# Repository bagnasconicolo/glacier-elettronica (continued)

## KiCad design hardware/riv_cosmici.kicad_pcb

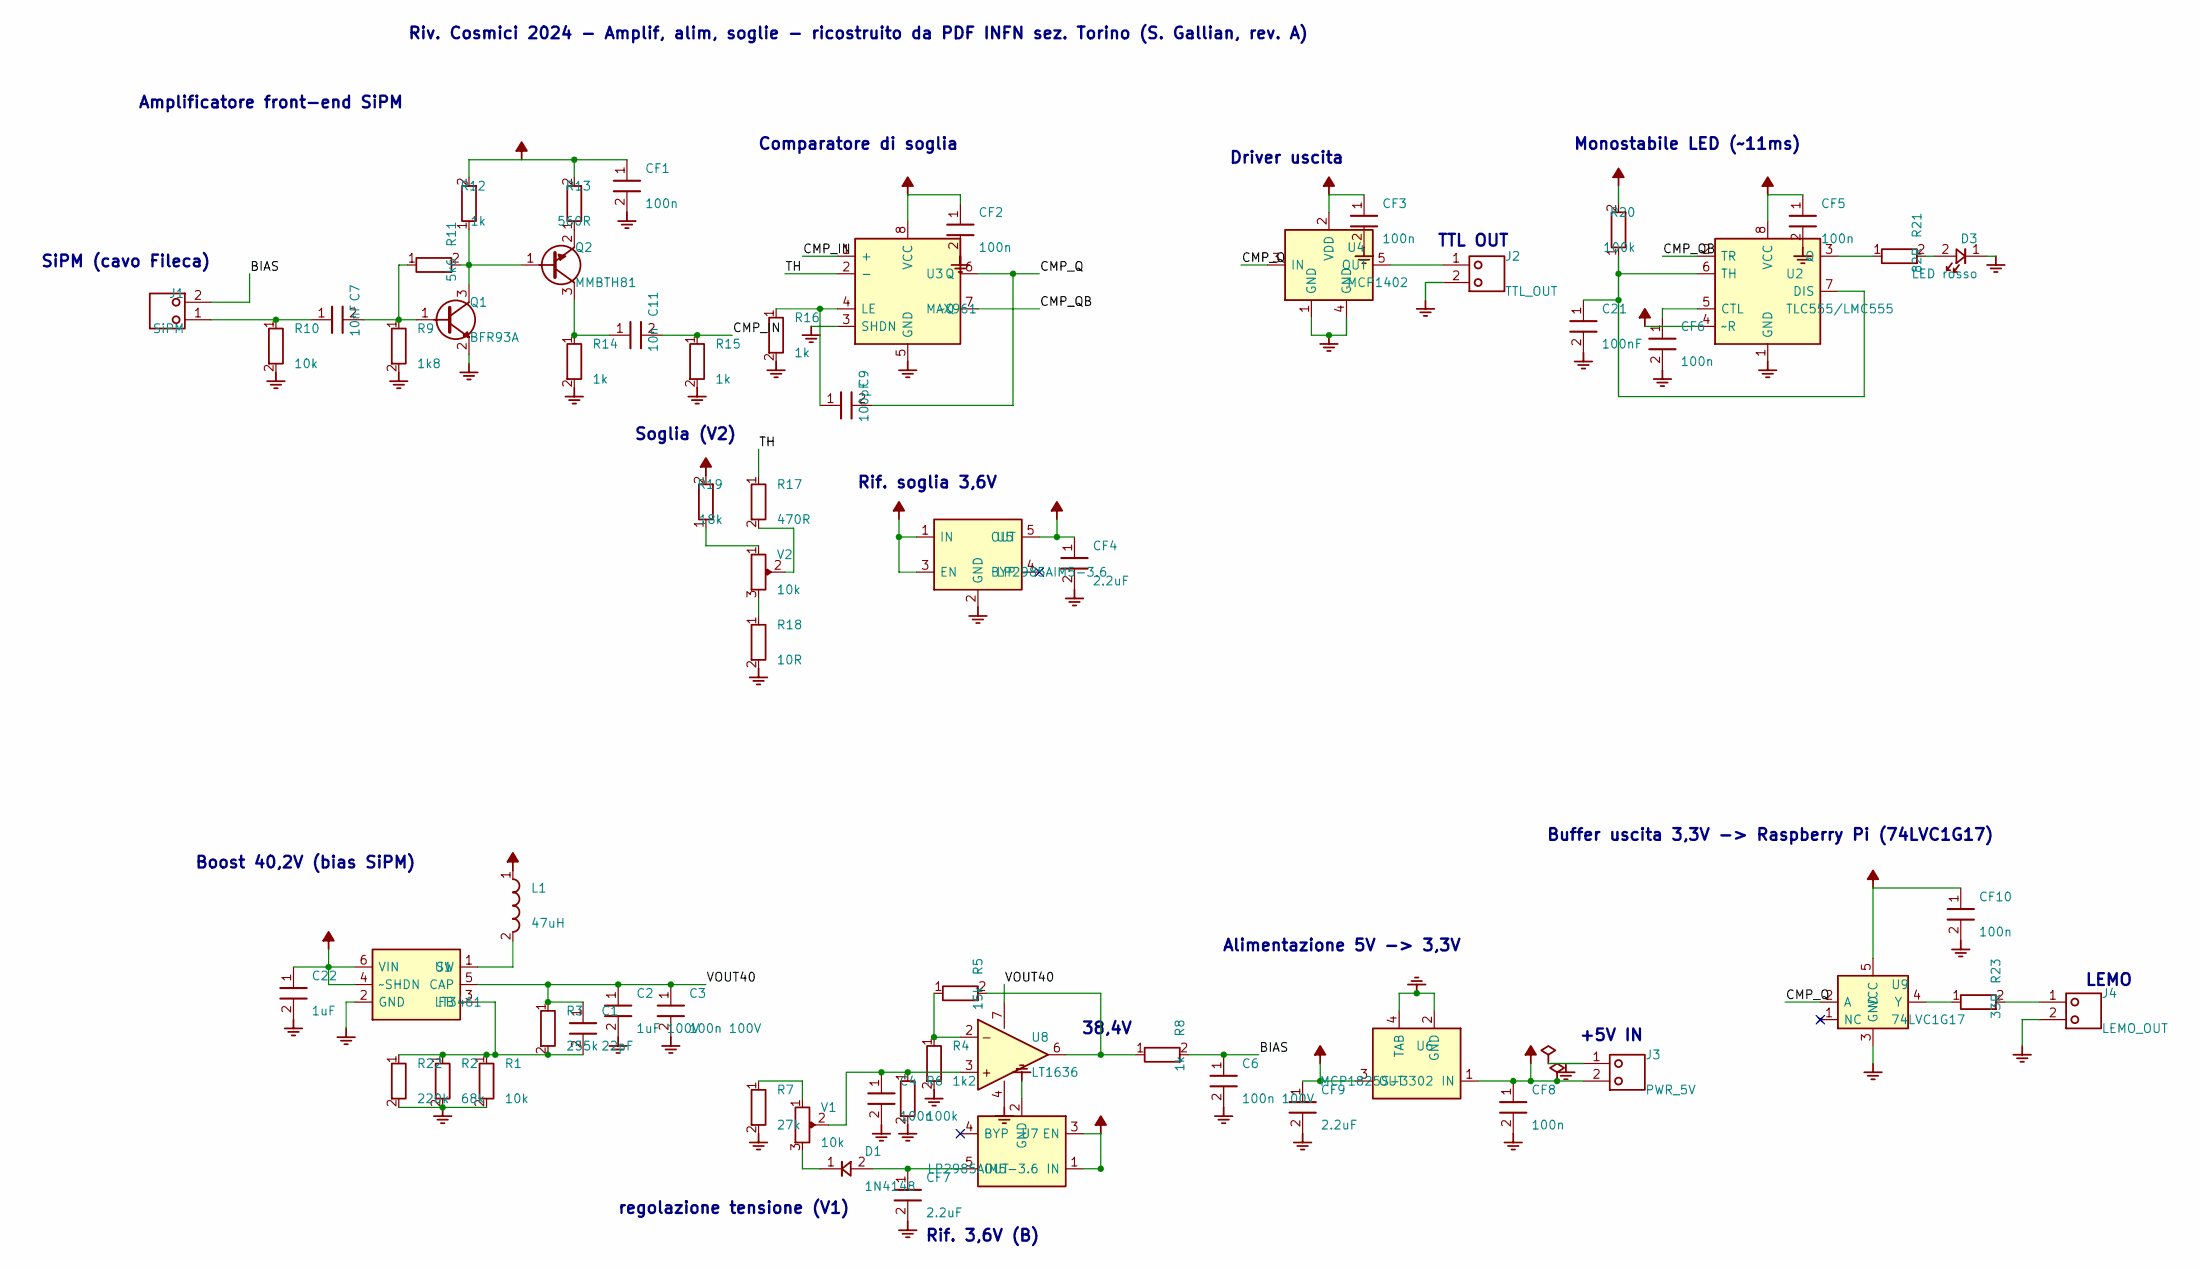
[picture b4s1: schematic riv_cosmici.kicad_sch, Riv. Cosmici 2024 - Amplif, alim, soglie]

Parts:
C1: 22pF; C_0805
C2: 1uF 100V; C_1210
C3, C6: 100n 100V; C_1206
C4: 100n; C_0805
C7: 10nF; C_0805
C9: 100pF; C_0805
C11: 10n; C_0805
C21: 100nF; C_0805
C22: 1uF; C_0805
CF1, CF2, CF3, CF5, CF6, CF8, CF10: 100n; C_0805
CF4, CF7, CF9: 2.2uF; C_0805
D1: 1N4148; D_DO35
D3: LED rosso; LED_0805
J1: SiPM; HDR1x02
J2: TTL_OUT; HDR1x02
J3: PWR_5V; HDR1x02
J4: LEMO_OUT; HDR1x02
L1: 47uH; L_PWR_5050
Q1: BFR93A; SOT23
Q2: MMBTH81; SOT23
R1, R10: 10k; R_0805
R2: 68k; R_0805
R3: 255k; R_0805
R4: 1k2; R_0805
R5: 15k; R_0805
R6, R20: 100k; R_0805
R7: 27k; R_0805
R8, R12, R14, R15, R16: 1k; R_0805
R9: 1k8; R_0805
R11: 5k6; R_0805
R13: 560R; R_0805
R17: 470R; R_0805
R18: 10R; R_0805
R19: 18k; R_0805
R21: 82R; R_0805
R22: 220k; R_0805
R23: 33R; R_0805
U1: LT3461; SOT23-6
U2: TLC555/LMC555; SOIC8
U3: MAX961; SOIC8
U4: MCP1402; SOT23-5
U5, U7: LP2985AIM5-3.6; SOT23-5
U6: MCP1825S-3302; SOT223
U8: LT1636; SOIC8
U9: 74LVC1G17; SOT23-5
V1, V2: 10k; TRIM_3296W

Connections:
+3V3: CF1.1, CF2.1, CF5.1, CF9.1, CF10.1, R12.2, R13.2, R20.2, U2.4 (~R), U2.8 (VCC), U3.8 (VCC), U6.3 (OUT), U9.5 (VCC)
+3V6: CF4.1, R19.2, U5.5 (OUT)
+5V: C22.1, CF3.1, CF8.1, J3.2, L1.1, U1.4 (~SHDN), U1.6 (VIN), U4.2 (VDD), U5.1 (IN), U5.3 (EN), U6.1 (IN), U7.1 (IN), U7.3 (EN)
/BIAS: C6.1, J1.2, R8.2
/CMP_IN: C11.2, R15.1, U3.1 (+)
/CMP_Q: C9.2, U3.6 (Q), U4.3 (IN), U9.2 (A)
/CMP_QB: U2.2 (TR), U3.7 (~Q)
/TH: R17.1, U3.2 (-)
/VOUT40: C1.1, C2.1, C3.1, R3.1, U1.5 (CAP), U8.7 (V+)
GND: C2.2, C3.2, C4.2, C6.2, C21.2, C22.2, CF1.2, CF2.2, CF3.2, CF4.2, CF5.2, CF6.2, CF7.2, CF8.2, CF9.2, CF10.2, D3.1 (K), J2.2, J3.1, J4.2, Q1.2 (E), R1.2, R2.2, R4.2, R6.2, R7.2, R9.2, R10.2, R14.2, R15.2, R16.2, R18.2, R22.2, U1.2 (GND), U2.1 (GND), U3.3 (SHDN), U3.5 (GND), U4.1 (GND), U4.4 (GND), U5.2 (GND), U6.2 (GND), U6.4 (TAB), U7.2 (GND), U8.4 (V-), U9.3 (GND)
unnamed: C7.1, J1.1, R10.1
unnamed: CF7.1, D1.2 (A), U7.5 (OUT)
unnamed: D1.1 (K), V1.3
unnamed: D3.2 (A), R21.2
unnamed: J4.1, R23.2
unnamed: C7.2, Q1.1 (B), R9.1, R11.1
unnamed: Q1.3 (C), Q2.1 (B), R11.2, R12.1
unnamed: C11.1, Q2.3 (C), R14.1
unnamed: Q2.2 (E), R13.1
unnamed: R5.2, R8.1, U8.6
unnamed: R7.1, V1.1
unnamed: R18.1, V2.3
unnamed: R19.1, V2.1
unnamed: C1.2, R1.1, R2.1, R3.2, R22.1, U1.3 (FB)
unnamed: L1.2, U1.1 (SW)
unnamed: CF6.1, U2.5 (CTL)
unnamed: C21.1, R20.1, U2.6 (TH), U2.7 (DIS)
unnamed: R21.1, U2.3 (Q)
unnamed: C9.1, R16.1, U3.4 (LE)
unnamed: J2.1, U4.5 (OUT)
unnamed: C4.1, R6.1, U8.3 (+), V1.2 (W)
unnamed: R4.1, R5.1, U8.2 (-)
unnamed: R23.1, U9.4 (Y)
unnamed: R17.2, V2.2 (W)

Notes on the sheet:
SiPM (cavo Fileca)
Amplificatore front-end SiPM
Comparatore di soglia
Soglia (V2)
Rif. soglia 3,6V
TTL OUT
Driver uscita
Monostabile LED (~11ms)
Boost 40,2V (bias SiPM)
38,4V
regolazione tensione (V1)
Rif. 3,6V (B)
+5V IN
Alimentazione 5V -> 3,3V
Buffer uscita 3,3V -> Raspberry Pi (74LVC1G17)
LEMO
Riv. Cosmici 2024 - Amplif, alim, soglie - ricostruito da PDF INFN sez. Torino (S. Gallian, rev. A)

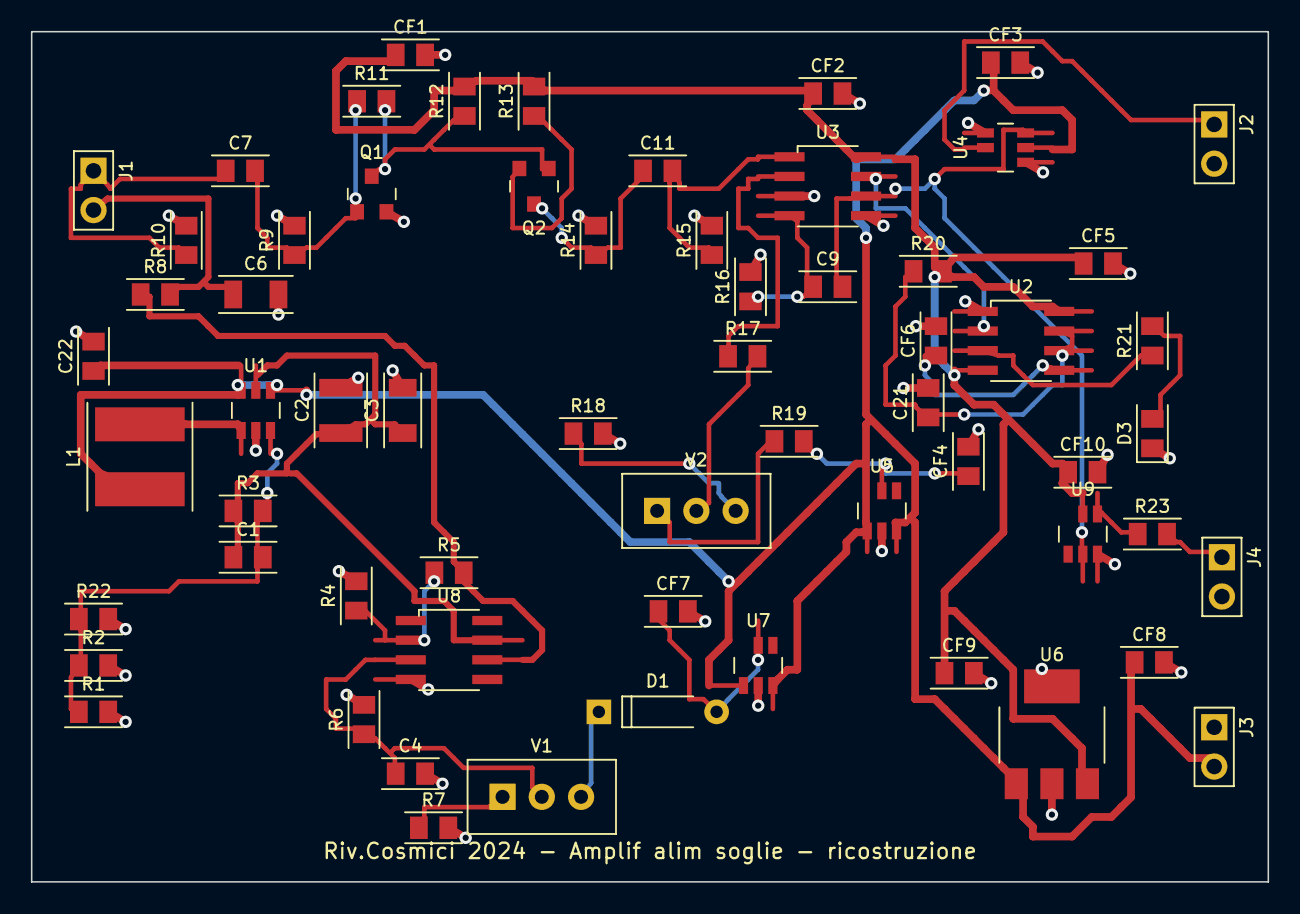
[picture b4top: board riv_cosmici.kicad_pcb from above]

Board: 2 copper layers, 80.0 x 55.0 mm, 63 parts (0 on the bottom side), 34 nets.

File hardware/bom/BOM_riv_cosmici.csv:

Rif.,Qta,Valore/Parte,Package,Codice ordine,Note
C1,1,22pF,0805,,
C2,1,1uF 100V,1210,,"dielettrico X7R, 100V (nodo VOUT40 ~41 V)"
C3 C6,2,100n 100V,1206,,"X7R 100V (nodi 40V/38,4V)"
C4 CF1 CF2 CF3 CF5 CF6 CF8 CF10,8,100n,0805,,X7R 50V (CF = disaccoppiamento)
C7,1,10nF,0805,,
C9,1,100pF,0805,,
C11,1,10n,0805,,
C21,1,100nF,0805,,
C22,1,1uF,0805,,
CF4 CF7 CF9,3,2.2uF,0805,,"X7R 0805 >= 10 V, es. Samsung CL21B225KAFNNNE (uscite regolatori; INFN: 100n)"
D1,1,1N4148,DO-35,,assiale DO-35 (o 1N4148W SOD-123 adattando il footprint)
D3,1,LED rosso,0805,,LED rosso 0805 (pin 1 = catodo)
J1,1,SiPM,Header 2.54 1x2,,"verso scintillatore, cavo Fileca schermato; calza = bias 38,4V"
J2,1,TTL_OUT,Header 2.54 1x2,,uscita 0-5 V (MCP1402): NON collegare ai GPIO del Raspberry Pi
J3,1,PWR_5V,Header 2.54 1x2,,"pin 1 = GND, pin 2 = +5V"
J4,1,LEMO_OUT,Header 2.54 1x2,,"uscita 0-3,3 V per GPIO Raspberry Pi; footprint header 2.54 -> LEMO a pannello via cavo"
L1,1,47uH,SMD 5x5/6x6,RS 693-4344,verificare l'ingombro della parte RS effettiva contro il footprint 5x5
Q1,1,BFR93A,SOT-23,RS 892-2365,
Q2,1,MMBTH81,SOT-23,RS 104-1196,
R1 R10,2,10k,0805,,
R2,1,68k,0805,,
R3,1,255k,0805,,"1% (INFN: 270k): VOUT40 39,4 V, sotto i 40 V max del LT3461"
R4,1,1k2,0805,,
R5,1,15k,0805,,
R6 R20,2,100k,0805,,
R7,1,27k,0805,,
R8 R12 R14 R15 R16,5,1k,0805,,
R9,1,1k8,0805,,
R11,1,5k6,0805,,
R13,1,560R,0805,,
R17,1,470R,0805,,
R18,1,10R,0805,,
R19,1,18k,0805,,
R21,1,82R,0805,,
R22,1,220k,0805,,
R23,1,33R,0805,,terminazione serie del cavo verso Raspberry Pi
U1,1,LT3461,SOT-23-6 (ThinSOT),Farnell 4024725,
U2,1,TLC555/LMC555,SO-8,RS 196-2112 (LMC555CM),
U3,1,MAX961,SO-8,RS 189-9176,
U4,1,MCP1402,SOT-23-5,RS 668-4203,
U5 U7,2,LP2985AIM5-3.6,SOT-23-5,RS 812-2417,
U6,1,MCP1825S-3302,SOT-223,RS 669-5092,
U8,1,LT1636,SO-8,Farnell 4020771,
U9,1,74LVC1G17,SOT-23-5,,"SN74LVC1G17DBVR (TI) o equivalente; buffer 3,3 V verso Raspberry Pi"
V1 V2,2,10k,Trimmer 3296W,,Bourns 3296W-1-103LF o equivalente
(fuori scheda),1,SiPM AFBR-S4N22P014M,-,Farnell 4351470,montato su PCB separato incollato allo scintillatore

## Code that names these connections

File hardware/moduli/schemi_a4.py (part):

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    # PPS
    y = 8.6
    s.text(1.8, 12.4, "USCITA PPS (dal GPS)", fs=8, weight="bold")
    s.label((9.0, y), "PPS_GPS (J6 pin 6)", side="left")
    s.pin("J6", 6, "PPS_GPS")
    s.comp("R", "R30", (9.2, y), "right", length=2.5, loc="top", nets=["PPS_GPS", "PPS"])
    s.wire((11.7, y), (17.0, y))
    s.dot((13.5, y)); s.comp("R", "R31", (13.5, y), "down", length=2.0, nets=["PPS", "GND"]); s.gnd((13.5, y - 2.0))
    s.dot((15.5, y)); s.wire((15.5, y), (15.5, y + 1.6)); s.label((15.5, y + 1.6), "GP6  (A1 pin 9)")
    s.pin("A1", 9, "PPS")
    b = s.add(logic.Buf().at((17.0, y)).right().anchor("in1").label("U5\n74LVC1G17", loc="top", fontsize=FS - 0.6))
    DRAWN.append((ACQ.NOME, "U5", ACQ.COMPONENTS["U5"][1]))
    s.pin("U5", 2, "PPS"); s.pin("U5", 4, "PPS_BUF"); s.pin("U5", 5, "+3V3"); s.pin("U5", 3, "GND")
    s.comp("R", "R32", b.out, "right", length=2.5, loc="bot", nets=["PPS_BUF", "PPS_OUT"])
    x = b.out[0] + 2.5
    s.wire((x, y), (x + 4.5, y))
    s.dot((x + 1.5, y)); s.tvs("D5", (x + 1.5, y)); s.pin("D5", 1, "PPS_OUT")
    s.lemo((x + 4.5, y), "J5", "PPS OUT", verso="left")
    s.pin("J5", 1, "PPS_OUT"); s.pin("J5", 2, "GND")
    s.text(30.0, y - 1.7, "U5: VCC +3V3, C5 100 nF", fs=FS - 1.8)
    DRAWN.append((ACQ.NOME, "C5", ACQ.COMPONENTS["C5"][1]))
    # note
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        s.dot((x, ap["5"][1])); s.comp("C", ref, (x, ap["5"][1]), "down", length=1.8, nets=["+3V3_QW", "GND"])
        s.gnd((x, ap["5"][1] - 1.8))
    s.dot((22.0, ap["5"][1]))
    s.comp("R", "R40", (22.0, ap["5"][1]), "down", length=1.6, loc="bot", nets=["+3V3_QW", "LED_PWR"])
    s.add(elm.LED().at((22.0, ap["5"][1] - 1.6)).down(1.4).label("D10\nverde", loc="bot", fontsize=FS - 1.0))
    DRAWN.append((ACQ.NOME, "D10", ACQ.COMPONENTS["D10"][1])); s.pin("D10", "2", "LED_PWR"); s.pin("D10", "1", "GND")
    s.gnd((22.0, ap["5"][1] - 3.0))
    s.label((26.0, y), "LED_ATT", side="left"); s.wire((26.0, y), (27.0, y))
    s.comp("R", "R41", (27.0, y), "right", length=2.0, loc="top", nets=["LED_ATT", "LED_ATT_K"])
    s.add(elm.LED().at((29.0, y)).down(1.6).label("D11", loc="bot", fontsize=FS - 1.0))
    DRAWN.append((ACQ.NOME, "D11", ACQ.COMPONENTS["D11"][1])); s.pin("D11", "2", "LED_ATT_K"); s.pin("D11", "1", "GND")
    s.gnd((29.0, y - 1.6))
    s.text(32.0, 6.6, "+5V: dalla USB del Pico (pin 40 VBUS)", fs=FS - 1.6)
    s.text(32.0, 5.6, "+3V3: regolatore del Pico (pin 36), max 300 mA", fs=FS - 1.6)
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
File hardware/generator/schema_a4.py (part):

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    s.gnd((xbias, op.out.y - 2.4))
    s.tp((xbias, op.out.y), "BIAS", "right")
    s.wire((xbias, op.out.y), (xbias, 22.3), (1.1, 22.3), (1.1, 34.7), (2.35, 34.7))
    s.text(xbias + 0.3, 21.85, "BIAS ~38,4 V -> catodo del SiPM (calza del cavo, J1 pin 2)", fs=FS - 1.0)
    # monitor del bias (ROSSO): 1M / 43k + 100n su VREG38 -> U11 (dentro l'anello: il bias non cambia)
    s.comp("R", r("R50"), (xout, op.out.y), "down", length=2.4, c=RED, loc="bot")
    ym = op.out.y - 2.4
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                (6, "VDD", "top", 2.3), (7, "SDA", "right", 5.0), (8, "SCL", "right", 3.6)],
               "U11\nMCP3424\n0x68", c=RED)
    DRAWN["U11"] = "MCP3424"
    for pin, lab in ((1, "MON1 ch1"), (3, "MON2 ch2"), (11, "MON3 ch3")):
        s.wire(u11[pin], (u11[pin][0] - 1.0, u11[pin][1]), c=RED)
        s.text(u11[pin][0] - 1.1, u11[pin][1], lab, c=RED, fs=FS - 1.3, ha="right")
    for pin in (2, 4, 12):
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                (6, "VDD", "top", 2.3), (7, "SDA", "right", 5.0), (8, "SCL", "right", 3.6)],
               "U12\nMCP3424", c=RED)
    DRAWN["U12"] = "MCP3424"
    for pin, lab in ((1, "MONTH1 ch1"), (3, "MONTH2 ch2"), (11, "MONTH3 ch3")):
        s.wire(u12[pin], (u12[pin][0] - 1.0, u12[pin][1]), c=RED)
        s.text(u12[pin][0] - 1.1, u12[pin][1], lab, c=RED, fs=FS - 1.3, ha="right")
    for pin in (2, 4, 12):
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
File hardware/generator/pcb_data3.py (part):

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    "J7":  (3.4, 17.0, 270),        # bordo scheda a x = 0 (bocca a filo, corpo +0,5 mm)
    "R60": (10.795, 16.0, 0),       # CC1 a massa
    "R61": (10.795, 18.0, 0),       # CC2 a massa
    "F1":  (14.605, 9.5, 90),       # pin 1 in basso (VIN_RAW), pin 2 in alto (VIN_F)
    "D5":  (14.605, 17.0, 90),      # pin 1 = catodo in basso (VIN_F), anodo in alto (GND)
    "Q4":  (14.605, 24.13, 0),      # drain in alto (VIN_F), gate/source in basso
    "R62": (11.43, 25.4, 90),
    "C60": (14.605, 28.575, 0),
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     ["JP1", "JP2", "JP3", "R31", "R32", "R33", "U10", "CF11", "R30", "TP5"]),
]
# etichette dei test point (testo accanto al foro)
TP_LABEL = {"TP01": "SiPM", "TP06": "GND", "TP05": "BIAS", "TP02": "IN",
            "TP03": "SOGLIA", "TP04": "OUT",
            "TP1": "40V", "TP2": "5V", "TP3": "3,3V", "TP4": "3,6V", "TP5": "AND", "TP6": "GND"}

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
